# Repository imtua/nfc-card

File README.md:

# ImtCard!

ImtCard is a digital NFC business card that has a LED on it. The copper ring or the NFC antennas actually harvest some electricity through its antenna from the phone or device and with that harvested electricity, the LED lights up, how cool is that!

I made this as a reference/example card for <a href="https://jams.hackclub.com/jam/hacker-card"><b>hacker card</b></a>, a program where you can learn how to make your own hacker card and get it for free. It contains an implementation of every common parts.

## Features:
- Runs on NFC technology.
- Can store a little data in it.
- Can light up a LED through harvesting electricity.
- Cool design!

## Schematics:

## PCB:

## 3d Overview:

## Conclusion:

You can actually get inspired from my project and try it yourself. This is completely made on EasyEDA and that is the reason .kicad_sch file is missing from pcb folder, but gerber zip file is present, so that won't be a problem. You can look at some other color of the same pcb at /assets/color inspo/ and look at the used assets on /assets/used assets/. 

Stardance Project Link: <a href="https://stardance.hackclub.com/projects/54091"><b>ImtCard</b></a>

Made by **Imtiaz** with the help of <a href="hackclub.com"><b>Hack Club</b></a>.

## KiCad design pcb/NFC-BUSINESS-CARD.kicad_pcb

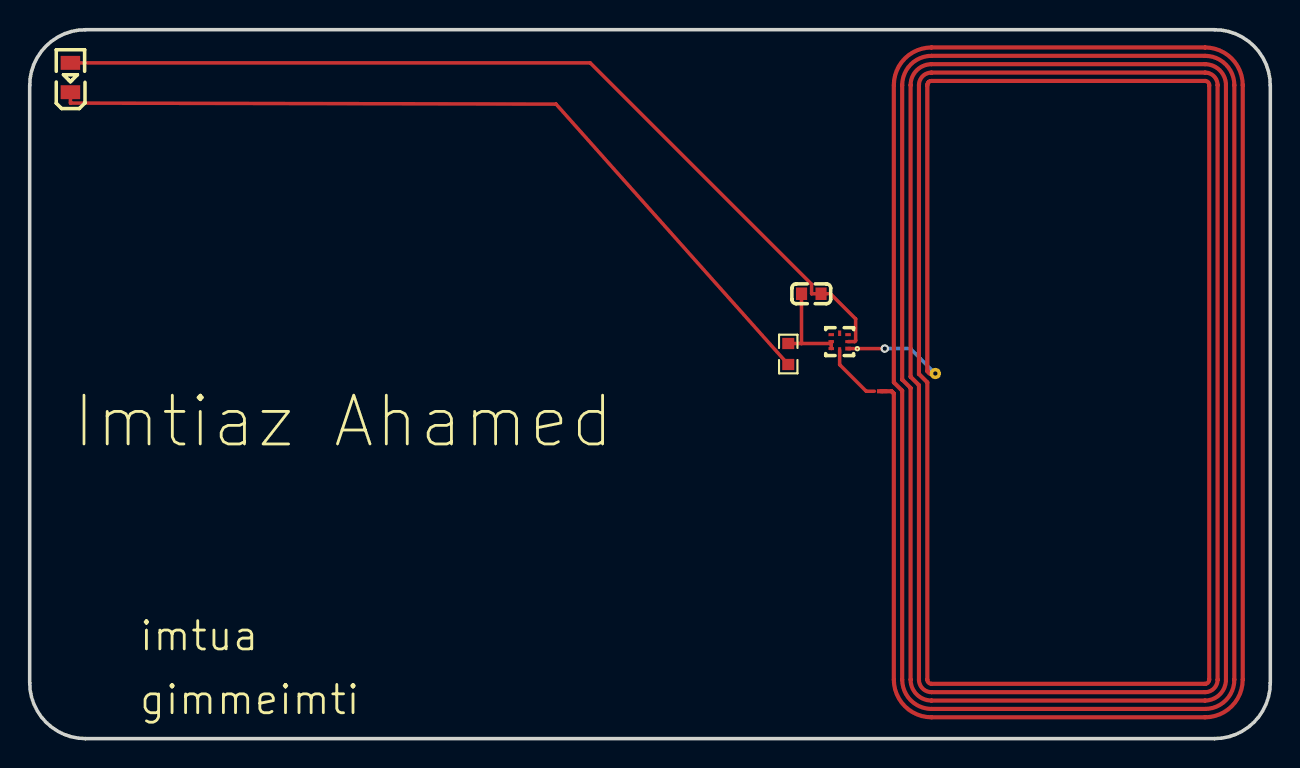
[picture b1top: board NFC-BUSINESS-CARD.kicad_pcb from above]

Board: 2 copper layers, 88.9 x 50.8 mm, 5 parts (0 on the bottom side), 5 nets.

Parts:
1: 25X48MM_NFC_ANTENNA
C1: 220nF; C0603
LED1: Yellow green 0805; LED0805-R-RD
R1: 47Ω; R0603
U1: NT3H2111W0FHKH; XQFN-8_L1.6-W1.6-P0.50-BL_NT3H2111W0FHKH

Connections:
LED1_2: LED1.2, R1.1
U1_1: 1.P$2, U1.1
U1_2: C1.1, LED1.1, U1.2
U1_6: C1.2, R1.2, U1.6, U1.7
U1_8: 1.P$1, U1.8
